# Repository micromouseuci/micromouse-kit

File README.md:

Starting new README for the BluePill Version thats work in progress!

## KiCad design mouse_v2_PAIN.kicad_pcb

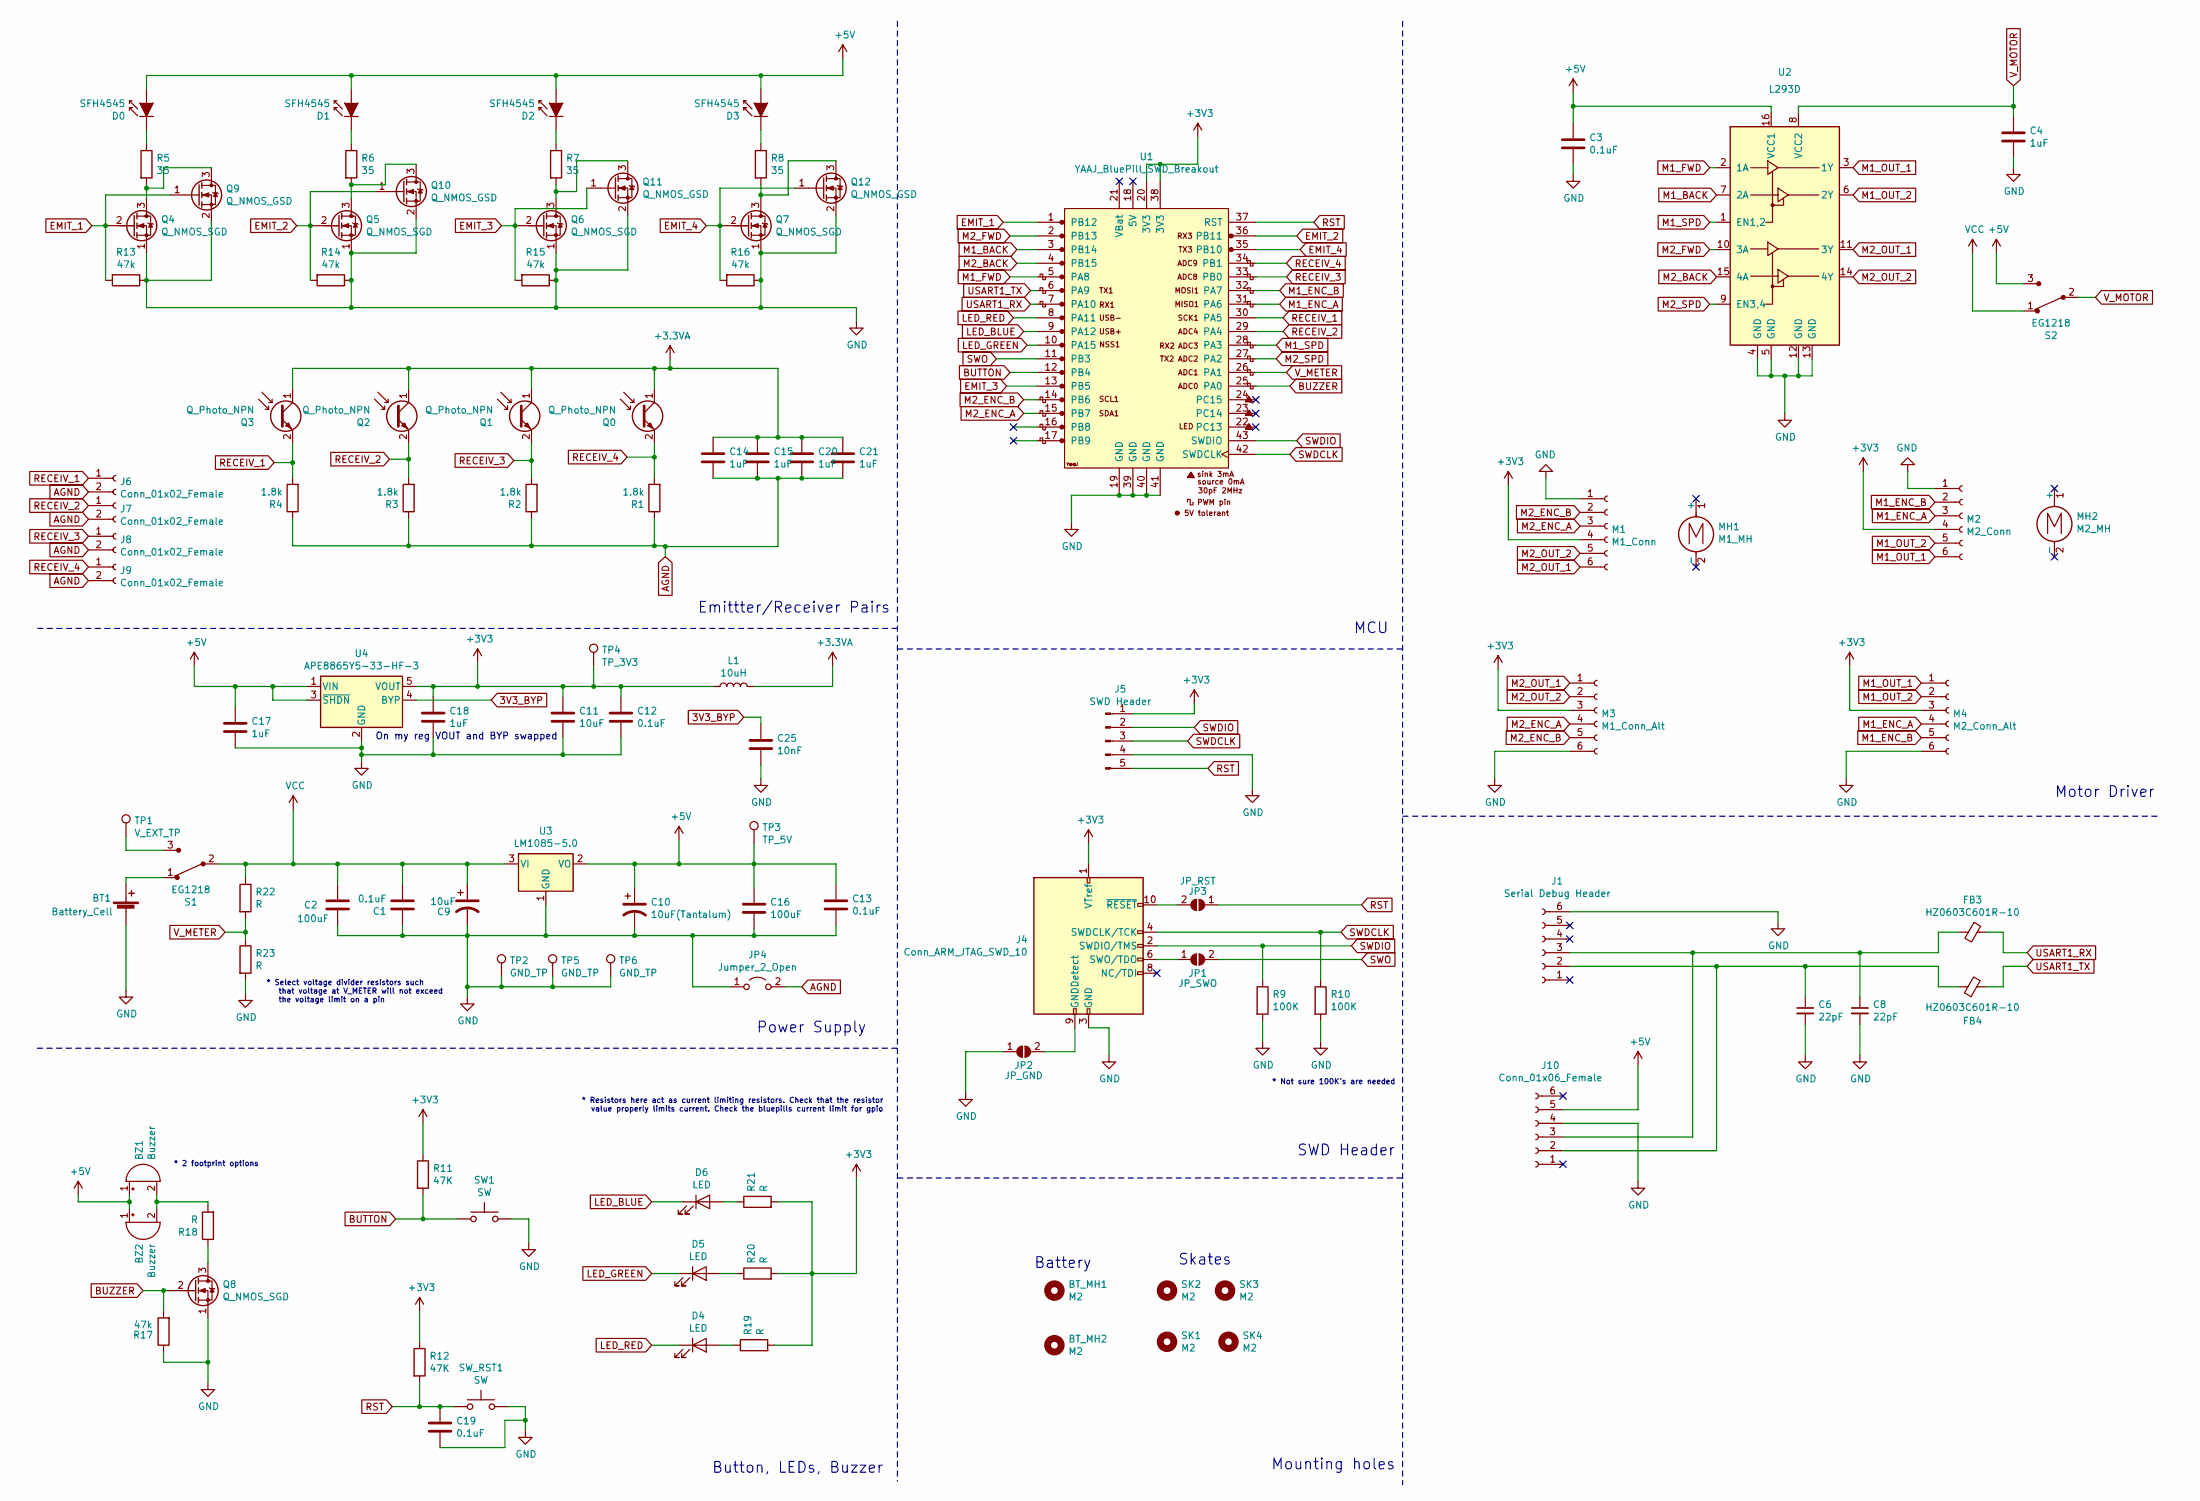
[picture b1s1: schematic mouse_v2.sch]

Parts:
BT1: Battery_Cell; PinSocket_1x02_P2.54mm_Vertical
BT_MH1, BT_MH2: M2; MountingHole_2.2mm_M2
BZ1: Buzzer; Buzzer_12x9.5RM7.6
BZ2: Buzzer; Buzzer_TDK_PS1240P02BT_D12.2mm_H6.5mm
C1, C3, C12, C13, C19: 0.1uF; C_1206_3216Metric_Pad1.33x1.80mm_HandSolder
C2, C16: 100uF; CP_Radial_D6.3mm_P2.50mm
C4, C14, C15, C17, C18, C20, C21: 1uF; C_1206_3216Metric_Pad1.33x1.80mm_HandSolder
C6, C8: 22pF; C_0603_1608Metric_Pad1.08x0.95mm_HandSolder
C9, C11: 10uF; C_1206_3216Metric_Pad1.33x1.80mm_HandSolder
C10: 10uF(Tantalum); C_1206_3216Metric_Pad1.33x1.80mm_HandSolder
C25: 10nF; C_1206_3216Metric_Pad1.33x1.80mm_HandSolder
D0, D1, D2, D3: SFH4545; Emitter
D4, D5, D6: LED; LED_0805_2012Metric_Pad1.15x1.40mm_HandSolder
FB3, FB4: HZ0603C601R-10; R_0603_1608Metric_Pad0.98x0.95mm_HandSolder
J1: Serial Debug Header; PinHeader_1x06_P2.54mm_Vertical
J4: Conn_ARM_JTAG_SWD_10; PinHeader_2x05_P1.27mm_Vertical
J5: SWD Header; PinHeader_1x05_P2.54mm_Vertical
J6, J7, J8, J9: Conn_01x02_Female; PinSocket_1x02_P2.00mm_Vertical
J10: Conn_01x06_Female; PinSocket_1x06_P2.54mm_Vertical
JP1: JP_SWO; SolderJumper-2_P1.3mm_Open_Pad1.0x1.5mm
JP2: JP_GND; SolderJumper-2_P1.3mm_Open_Pad1.0x1.5mm
JP3: JP_RST; SolderJumper-2_P1.3mm_Open_Pad1.0x1.5mm
JP4: Jumper_2_Open; SolderJumper-2_P1.3mm_Bridged_Pad1.0x1.5mm
L1: 10uH; L_1206_3216Metric_Pad1.42x1.75mm_HandSolder
M1: M1_Conn; JST_SH_BM06B-SRSS-TB_1x06-1MP_P1.00mm_Vertical
M2: M2_Conn; JST_SH_BM06B-SRSS-TB_1x06-1MP_P1.00mm_Vertical
M3: M1_Conn_Alt; PinHeader_1x06_P2.54mm_Vertical
M4: M2_Conn_Alt; PinHeader_1x06_P2.54mm_Vertical
MH1: M1_MH; Motor_mouse
MH2: M2_MH; Motor_mouse
Q0, Q1, Q2, Q3: Q_Photo_NPN; Emitter
Q4, Q5, Q6, Q7, Q8: Q_NMOS_SGD; TO-92
Q9, Q10, Q11, Q12: Q_NMOS_GSD; SOT-23
R1, R2, R3, R4: 1.8k; R_1206_3216Metric_Pad1.30x1.75mm_HandSolder
R5, R6, R7, R8: 35; R_1206_3216Metric_Pad1.30x1.75mm_HandSolder
R9, R10: 100K; R_1206_3216Metric_Pad1.30x1.75mm_HandSolder
R11, R12: 47K; R_1206_3216Metric_Pad1.30x1.75mm_HandSolder
R13, R14, R15, R16, R17: 47k; R_1206_3216Metric_Pad1.30x1.75mm_HandSolder
R18, R19, R20, R21, R22, R23: R; R_1206_3216Metric_Pad1.30x1.75mm_HandSolder
S1, S2: EG1218; 1103M2S4CQE2; MPN EG1218; Digi-Key_PN EG1903-ND
SK1, SK2, SK3, SK4: M2; MountingHole_2.2mm_M2
SW1: SW; SW_SPST_REED_CT05-XXXX-G1
SW_RST1: SW; SW_SPST_REED_CT05-XXXX-G1
TP1: V_EXT_TP; PinHeader_1x01_P2.54mm_Vertical
TP2, TP5, TP6: GND_TP; PinHeader_1x01_P2.54mm_Vertical
TP3: TP_5V; PinHeader_1x01_P2.54mm_Vertical
TP4: TP_3V3; PinHeader_1x01_P2.54mm_Vertical
U1: YAAJ_BluePill_SWD_Breakout; YAAJ_BluePill_SWD_2
U2: L293D; DIP-16_W7.62mm
U3: LM1085-5.0; VREG_TO-263-3_TabPin2
U4: APE8865Y5-33-HF-3; SOT-23-5

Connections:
3V3_BYP: C25.1, U4.4 (BYP)
+3.3VA: C14.1, C15.1, C20.1, C21.1, L1.2, Q0.1 (C), Q1.1 (C), Q2.1 (C), Q3.1 (C)
+3V3: C11.1, C12.1, C18.1, J4.1 (VTref), J5.1, L1.1, M1.4, M2.4, M3.3, M4.3, R11.1, R12.1, R19.2, R20.2, R21.2, TP4.1, U1.20 (3V3), U1.38 (3V3), U4.5 (VOUT)
+5V: BZ1.1 (-), BZ2.1 (-), C3.1, C10.1, C13.1, C16.1, C17.1, D0.2 (A), D1.2 (A), D2.2 (A), D3.2 (A), J10.5, S2.3, TP3.1, U2.16 (VCC1), U3.2 (VO), U4.1 (VIN), U4.3 (~SHDN~)
AGND: C14.2, C15.2, C20.2, C21.2, J6.2, J7.2, J8.2, J9.2, JP4.2 (B), R1.1, R2.1, R3.1, R4.1
BUTTON: R11.2, SW1.1, U1.12 (PB4)
BUZZER: Q8.2 (G), R17.2, U1.25 (PA0)
EMIT_1: Q4.2 (G), Q9.1 (G), R13.2, U1.1 (PB12)
EMIT_2: Q5.2 (G), Q10.1 (G), R14.2, U1.36 (PB11)
EMIT_3: Q6.2 (G), Q11.1 (G), R15.2, U1.13 (PB5)
EMIT_4: Q7.2 (G), Q12.1 (G), R16.2, U1.35 (PB10)
GND: BT1.2 (-), C1.1, C2.2, C3.2, C4.2, C6.2, C8.2, C9.2, C10.2, C11.2, C12.2, C13.2, C16.2, C17.2, C18.2, C19.2, C25.2, J1.6, J4.3 (GND), J4.5 (GND), J5.4, J10.4, JP2.1 (A), JP4.1 (A), M1.1, M2.1, M3.6, M4.6, Q4.1 (S), Q5.1 (S), Q6.1 (S), Q7.1 (S), Q8.1 (S), Q9.2 (S), Q10.2 (S), Q11.2 (S), Q12.2 (S), R9.2, R10.2, R13.1, R14.1, R15.1, R16.1, R17.1, R23.2, SW1.2, SW_RST1.2, TP2.1, TP5.1, TP6.1, U1.19 (GND), U1.39 (GND), U1.40 (GND), U1.41 (GND), U2.4 (GND), U2.5 (GND), U2.12 (GND), U2.13 (GND), U3.1 (GND), U4.2 (GND); also elsewhere on the board
LED_BLUE: D6.1 (K), U1.9 (PA12)
LED_GREEN: D5.1 (K), U1.10 (PA15)
LED_RED: D4.1 (K), U1.8 (PA11)
M1_BACK: U1.3 (PB14), U2.7 (2A)
M1_ENC_A: M2.3, M4.4, U1.31 (PA6)
M1_ENC_B: M2.2, M4.5, U1.32 (PA7)
M1_FWD: U1.5 (PA8), U2.2 (1A)
M1_OUT_1: M2.6, M4.1, U2.3 (1Y)
M1_OUT_2: M2.5, M4.2, U2.6 (2Y)
M1_SPD: U1.28 (PA3), U2.1 (EN1,2)
M2_BACK: U1.4 (PB15), U2.15 (4A)
M2_ENC_A: M1.3, M3.4, U1.15 (PB7)
M2_ENC_B: M1.2, M3.5, U1.14 (PB6)
M2_FWD: U1.2 (PB13), U2.10 (3A)
M2_OUT_1: M1.6, M3.1, U2.11 (3Y)
M2_OUT_2: M1.5, M3.2, U2.14 (4Y)
M2_SPD: U1.27 (PA2), U2.9 (EN3,4)
unnamed: BT1.1 (+), S1.1
unnamed: BZ1.2 (+), BZ2.2 (+), R18.2
unnamed: C6.1, FB4.1, J1.2, J10.2
unnamed: C8.1, FB3.2, J1.3, J10.3
unnamed: D0.1 (K), R5.1
unnamed: D1.1 (K), R6.1
unnamed: D2.1 (K), R7.1
unnamed: D3.1 (K), R8.1
unnamed: D4.2 (A), R19.1
unnamed: D5.2 (A), R20.1
unnamed: D6.2 (A), R21.1
unnamed 43: J4.6 (SWO/TDO), JP1.1 (A); also elsewhere on the board
unnamed 46: J4.9 (GNDDetect), JP2.2 (B); also elsewhere on the board
unnamed 47: J4.10 (~RESET~), JP3.2 (B); also elsewhere on the board
unnamed: Q4.3 (D), Q9.3 (D), R5.2
unnamed: Q8.3 (D), R18.1
unnamed: Q5.3 (D), Q10.3 (D), R6.2
unnamed: Q6.3 (D), Q11.3 (D), R7.2
unnamed: Q7.3 (D), Q12.3 (D), R8.2
unnamed: S1.3, TP1.1
RECEIV_1: J6.1, Q3.2 (E), R4.2, U1.30 (PA5)
RECEIV_2: J7.1, Q2.2 (E), R3.2, U1.29 (PA4)
RECEIV_3: J8.1, Q1.2 (E), R2.2, U1.33 (PB0)
RECEIV_4: J9.1, Q0.2 (E), R1.2, U1.34 (PB1)
RST: C19.1, J5.5, JP3.1 (A), R12.2, SW_RST1.1, U1.37 (RST); also elsewhere on the board
SWDCLK: J4.4 (SWDCLK/TCK), J5.3, R10.1, U1.42 (SWDCLK)
SWDIO: J4.2 (SWDIO/TMS), J5.2, R9.1, U1.43 (SWDIO)
SWO: JP1.2 (B), U1.11 (PB3); also elsewhere on the board
USART1_RX: FB3.1, U1.7 (PA10)
USART1_TX: FB4.2, U1.6 (PA9)
VCC: C1.2, C2.1, C9.1, R22.1, S1.2, S2.1, U3.3 (VI)
V_METER: R22.2, R23.1, U1.26 (PA1)
V_MOTOR: C4.1, S2.2, U2.8 (VCC2)

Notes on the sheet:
Emittter/Receiver Pairs
Button, LEDs, Buzzer
Power Supply
MCU
SWD Header
Mounting holes
Skates
Battery
Motor Driver
* 2 footprint options
* Not sure 100K’s are needed
* Select voltage divider resistors such that voltage at V_METER will not exceed the voltage limit on a pin
* Resistors here act as current limiting resistors. Check that the resistor value properly limits current. Check the bluepills current limit for gpio
On my reg VOUT and BYP swapped

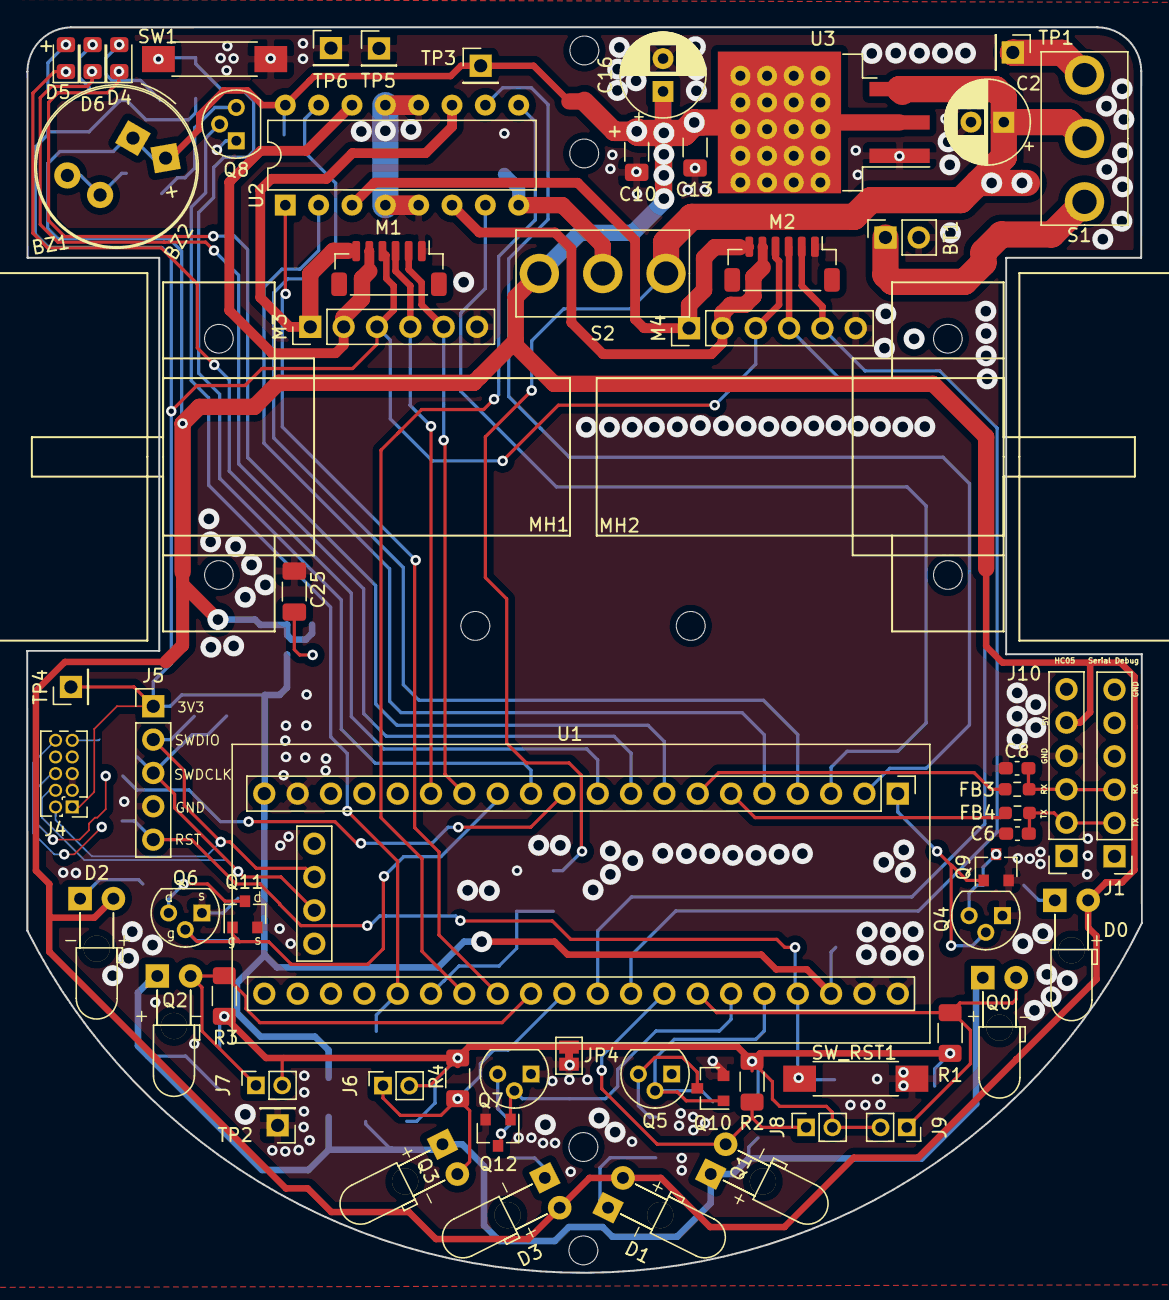
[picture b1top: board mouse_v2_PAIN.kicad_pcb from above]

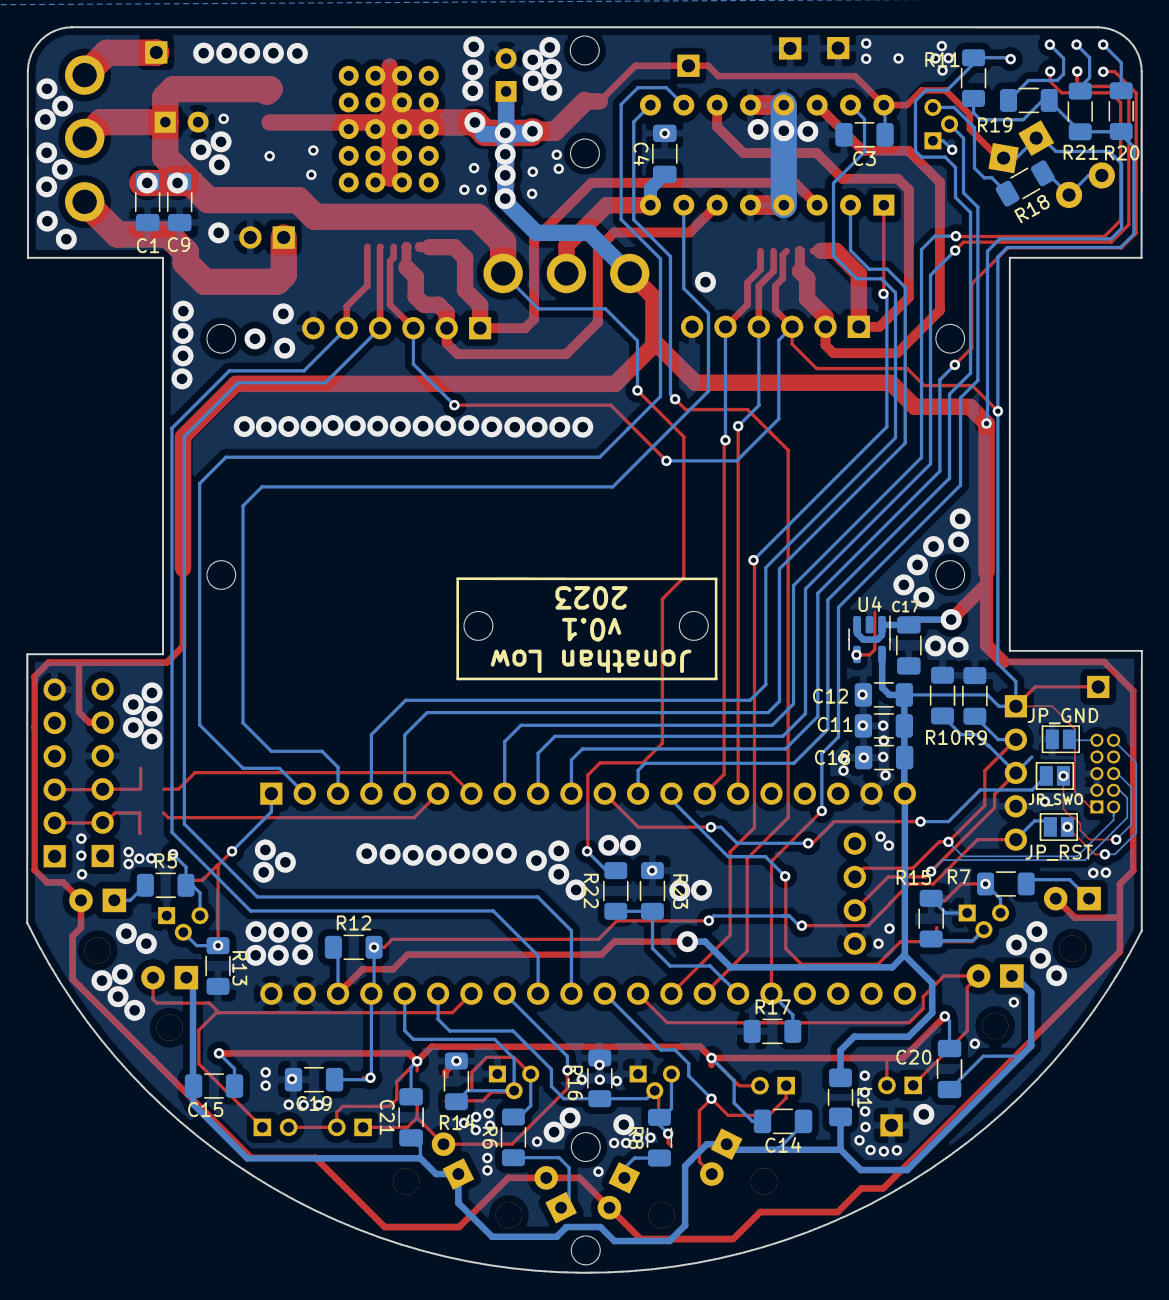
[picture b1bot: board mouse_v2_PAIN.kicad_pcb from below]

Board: 2 copper layers, 84.9 x 94.9 mm, 107 parts (37 on the bottom side), 62 nets.

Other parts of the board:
JP_GND: JP_GND; SolderJumper-2_P1.3mm_Open_Pad1.0x1.5mm
JP_RST: JP_RST; SolderJumper-2_P1.3mm_Open_Pad1.0x1.5mm
JP_SWO: JP_SWO; SolderJumper-2_P1.3mm_Open_Pad1.0x1.5mm

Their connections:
GND: JP_GND.1; also elsewhere on the board
unnamed 43: JP_SWO.1; also elsewhere on the board
unnamed 46: JP_GND.2; also elsewhere on the board
unnamed 47: JP_RST.2; also elsewhere on the board
RST: JP_RST.1; also elsewhere on the board
SWO: JP_SWO.2; also elsewhere on the board

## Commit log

2021-07-19 upload
2021-10-17 Add files via upload
    Fixed voltage meter connection from pin 26 to 30. Connection of resistor for buzzer(?)
2021-10-17 Fixed V1 errors
    Connected Buzzer circuit to gnd
    Connected Volt meter to analog pin
2022-05-06 updated motor offset
2022-06-02 Revert "Add files via upload"
2022-09-17 more shcem updates
2022-10-21 started work on pcb
2022-10-24 more tracing
2022-10-27 tracing
2022-11-01 label cleanup
2023-01-27 v0 PCB
2023-02-01 changes for v0.1 wip
2023-02-02 minor
2023-02-07 v0.1 ordered
